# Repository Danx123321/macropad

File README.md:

# macropad
Very cool macropad you can use and be the coolest person ever to assamble it

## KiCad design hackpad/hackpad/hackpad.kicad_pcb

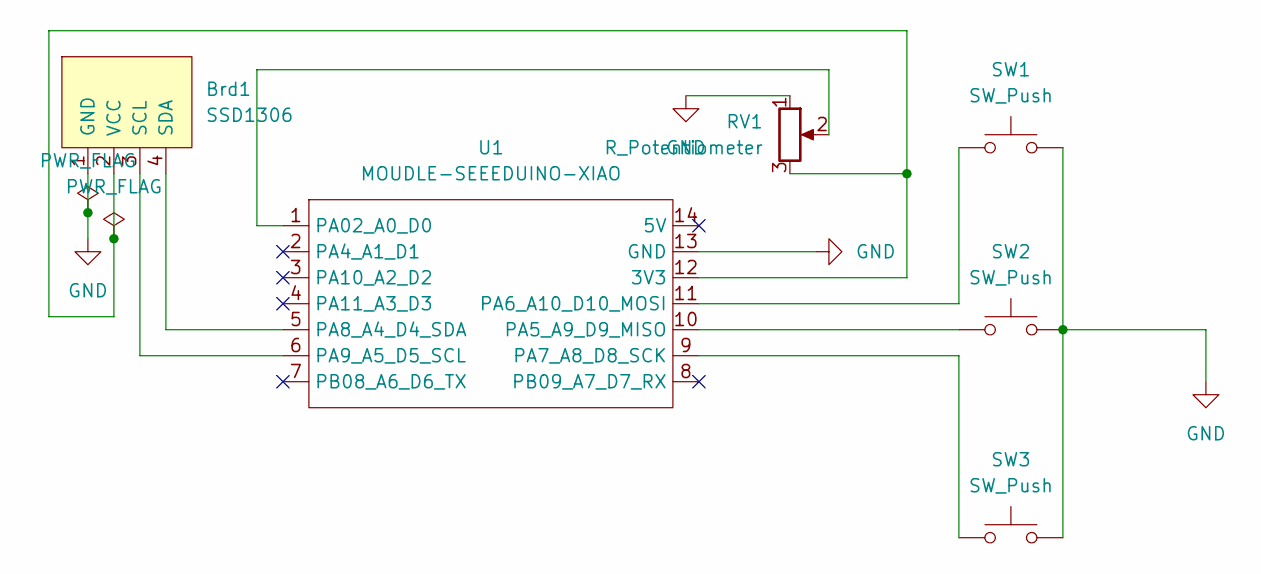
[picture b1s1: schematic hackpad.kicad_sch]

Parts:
Brd1: SSD1306; Adafruit_SSD1306
RV1: R_Potentiometer; Potentiometer_Bourns_PTA2043_Single_Slide
SW1, SW2, SW3: SW_Push; SW_Cherry_MX_1.00u_PCB
U1: MOUDLE-SEEEDUINO-XIAO; XIAO-Generic-Hybrid-14P-2.54-21X17.8MM

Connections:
GND: Brd1.1 (GND), RV1.1, SW1.2, SW2.2, SW3.2, U1.13 (GND)
unnamed: Brd1.3 (SCL), U1.6 (PA9_A5_D5_SCL)
unnamed: Brd1.4 (SDA), U1.5 (PA8_A4_D4_SDA)
unnamed: Brd1.2 (VCC), RV1.3, U1.12 (3V3)
unnamed: RV1.2, U1.1 (PA02_A0_D0)
unnamed: SW2.1, U1.10 (PA5_A9_D9_MISO)
unnamed: SW1.1, U1.11 (PA6_A10_D10_MOSI)
unnamed: SW3.1, U1.9 (PA7_A8_D8_SCK)

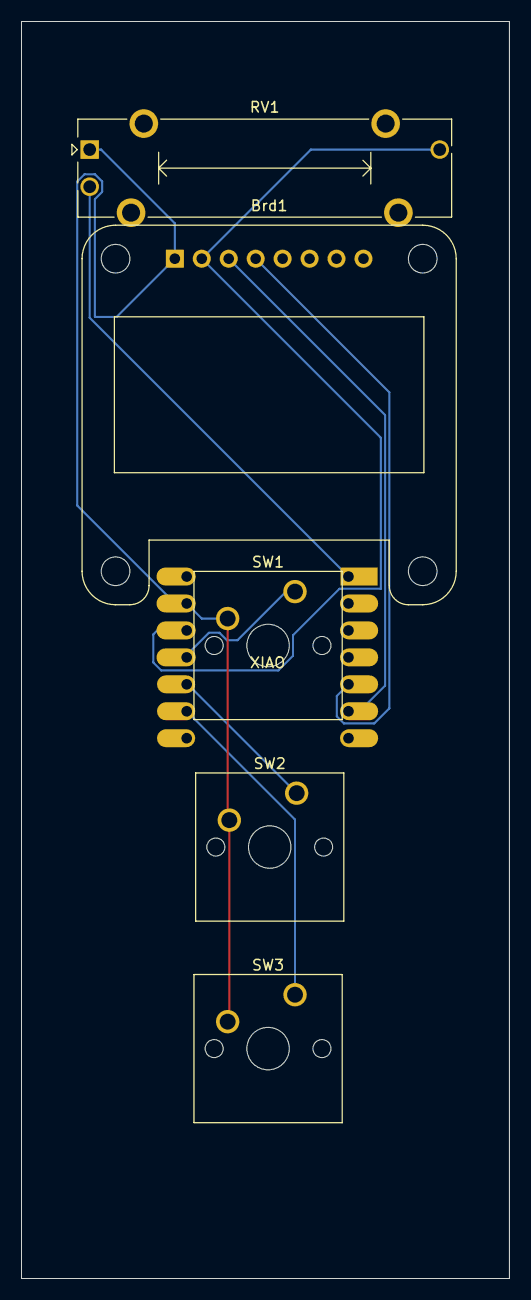
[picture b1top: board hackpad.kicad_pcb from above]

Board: 2 copper layers, 46.0 x 118.5 mm, 6 parts (1 on the bottom side), 8 nets.
